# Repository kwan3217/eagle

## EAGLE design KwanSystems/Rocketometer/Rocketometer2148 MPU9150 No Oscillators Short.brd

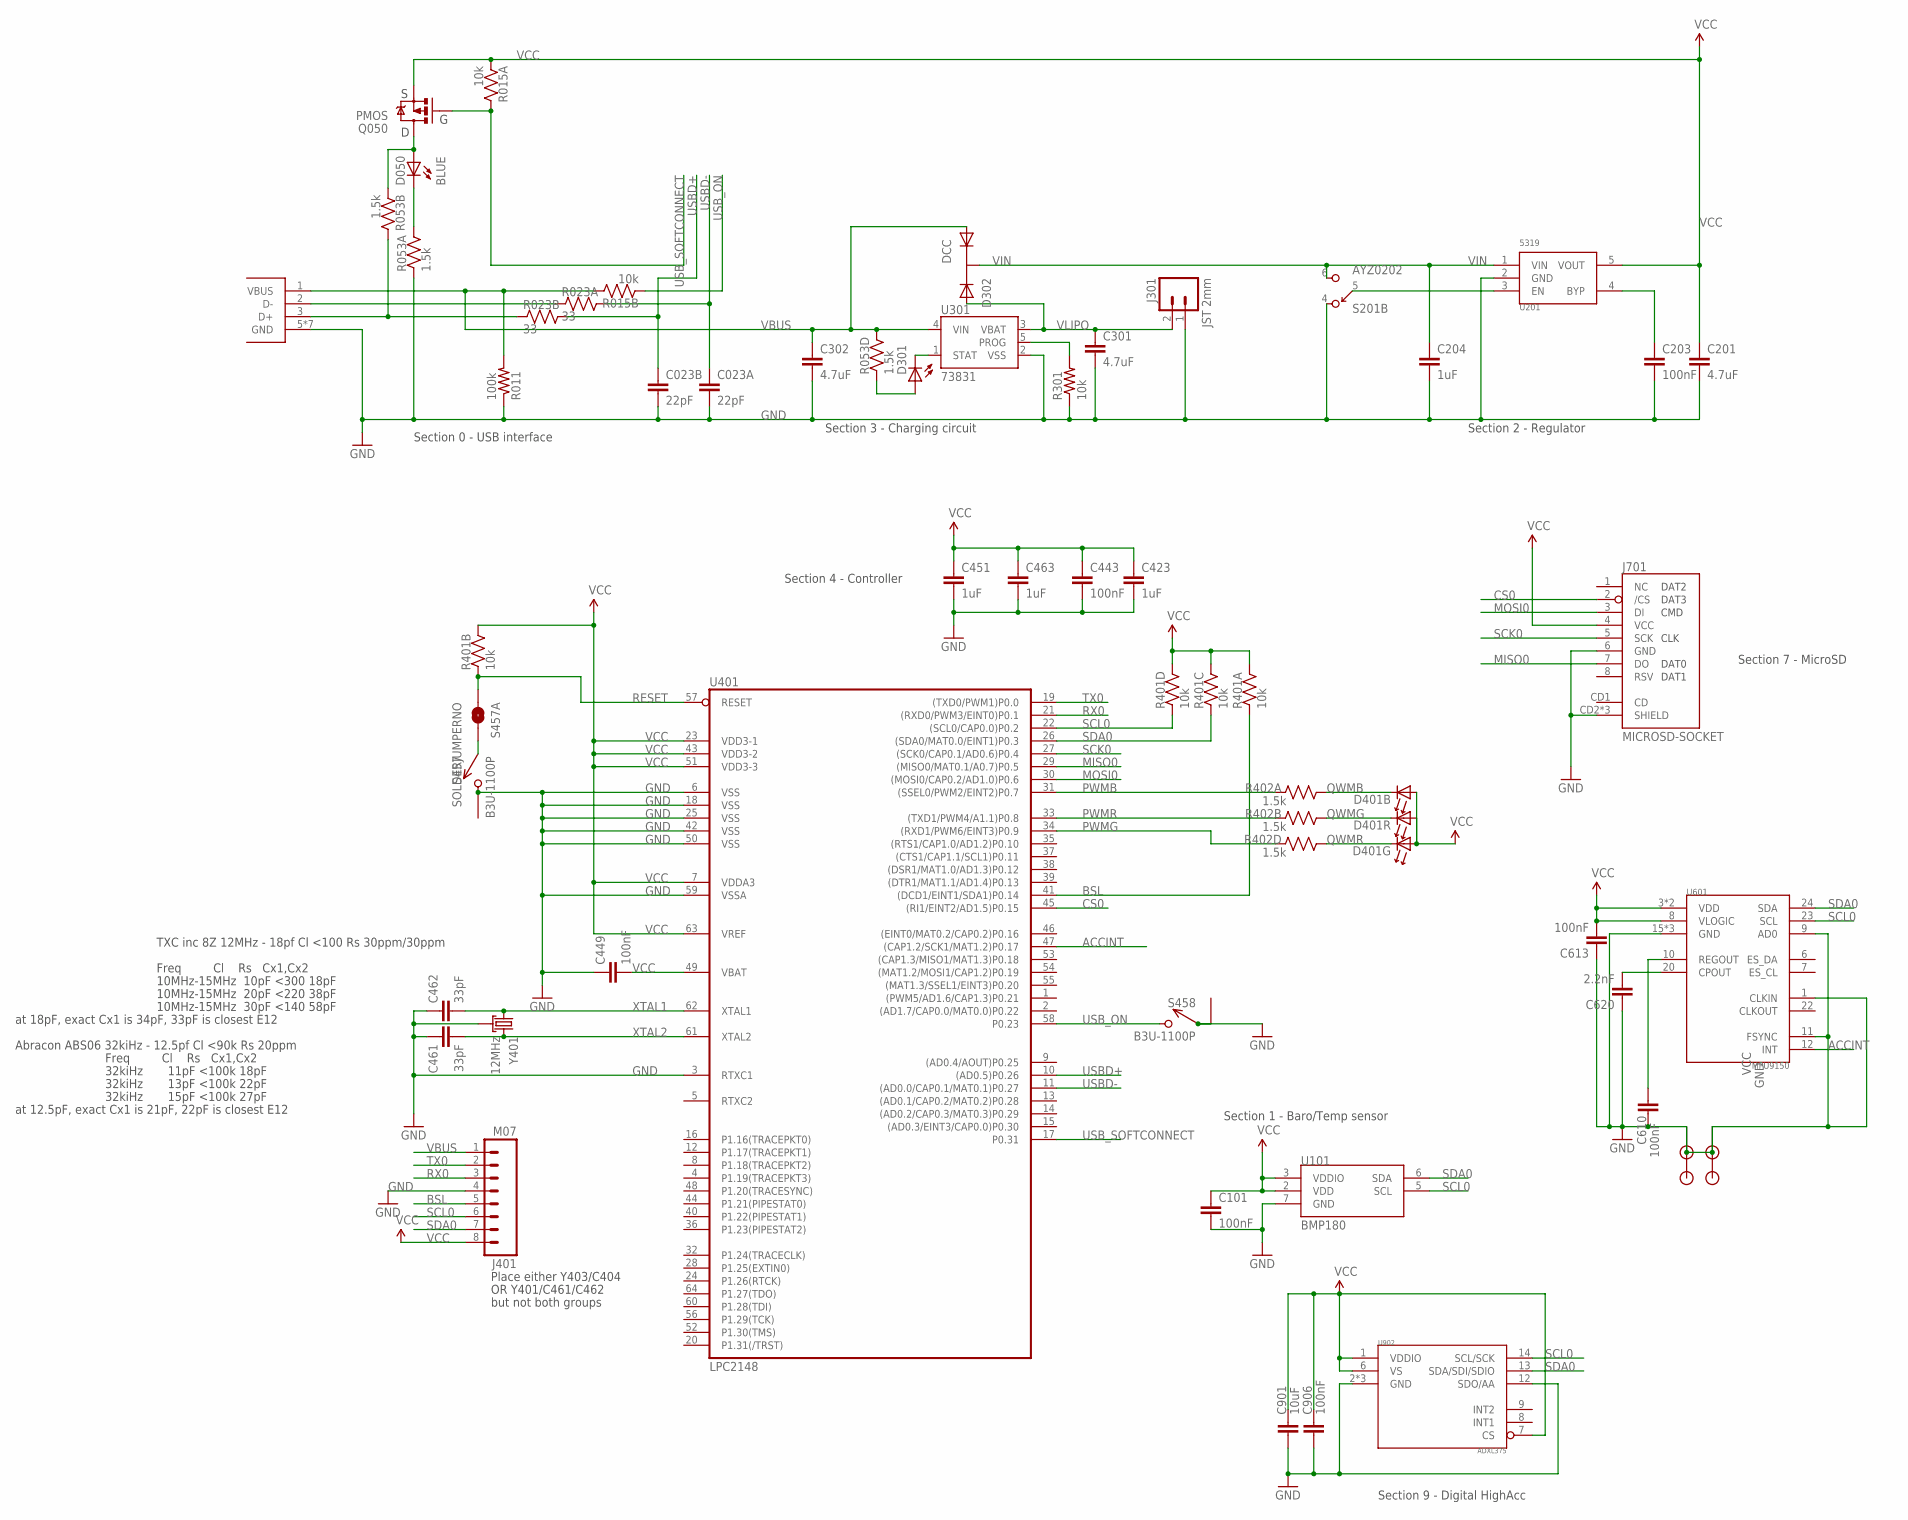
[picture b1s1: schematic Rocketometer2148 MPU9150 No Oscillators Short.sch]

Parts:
C023: 22pF; CKCM25; DIGIKEY 445-1860-1-ND
C101, C203, C443, C449, C610, C613, C906: 100nF; 0402-CAP; DIGIKEY 445-1265-1-ND
C201, C301, C302: 4.7uF; 0402-CAP; DIGIKEY 445-7395-1-ND
C204, C423, C451, C463: 1uF; 0402-CAP; DIGIKEY 445-4114-1-ND
C461, C462: 33pF; 0402-CAP; DIGIKEY 445-1241-1-ND
C620: 2.2nF; 0402-CAP; DIGIKEY 445-1257-1-ND
C901: 10uF; 0603-CAP; DIGIKEY 445-7486-1-ND
D050: BLUE; LED-0603; DIGIKEY 350-2037-1-ND
D301: YELLOW; LED-0603; DIGIKEY 350-2032-1-ND
D302: DCC; SOT-23-3; DIGIKEY 568-6500-1-ND
D401: SMLP36RGB2W(R); SMLP36; DIGIKEY 846-1097-1-ND
J001: USB_MICROB_JSTGCT; USB_MICROB_3075; DIGIKEY 609-4616-2-ND
J301: JST 2mm; JST-2-SMD; DIGIKEY 455-1749-1-ND
J401: M07; 1X08; DIGIKEY $NOPART
J701: MICROSD-SOCKET; MICROSD-SOCKET-PP; DIGIKEY 101-00581-59-1-ND
JP1, JP2, JP4, JP5: STANDOFF; DIGIKEY $NOPART
Q050: PMOS; SOT23-3; DIGIKEY NTR1P02T1GOSCT-ND
R011: 100k; 0402-RES; DIGIKEY P100KLCT-ND
R015: 10k; CRA02; DIGIKEY Y5103CT-ND
R023: 33; CRA02
R053, R402: 1.5k; CRA04; DIGIKEY CRA4S81.5KCT-ND
R301: 10k; 0402-RES; DIGIKEY P10.0KLCT-ND
R401: 10k; CRA04; DIGIKEY CRA4S810KCT-ND
S201: AYZ0202; DIGIKEY 401-2013-1-ND
S457, S458: B3U-1100P; DIGIKEY SW1021CT-ND
S457A: SOLDERJUMPERNO; SJ_2S-NO; DIGIKEY $NOPART
U101: BMP180; DIGIKEY 828-1027-1-ND
U201: 5319; SOT-23-5; DIGIKEY 576-1910-1-ND
U301: 73831; SOT23-5; DIGIKEY MCP73831T-2ACI/OTCT-ND
U401: LPC2148; SQFP-S-10X10-64; DIGIKEY 568-1765-ND
U601: MPU9150; LLGA24; DIGIKEY $NOPART
U902: ADXL375; DIGIKEY ADXL375BCCZ-ND
Y401: 12MHz; CRYSTAL_SMD_2MM_2_5MM; DIGIKEY 887-1487-1-ND

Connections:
ACCINT: U401.47 ((CAP1.2/SCK1/MAT1.2)P0.17), U601.12 (INT)
BSL: J401.5, R401.1, U401.41 ((DCD1/EINT1/SDA1)P0.14)
CONN_D+: J001.3 (D+), R023.2 (1), R053.7 (2)
CONN_D-: J001.2 (D-), R023.1
CS0: J701.2 (/CS), U401.45 ((RI1/EINT2/AD1.5)P0.15)
EN: S201.5, U201.3 (EN)
GND: C023.3 (2), C023.4 (2), C101.2, C201.2, C203.2, C204.2, C301.2, C302.2, C423.2, C443.2, C449.1, C451.2, C461.1, C462.1, C463.2, C610.2, C613.1, C620.1, C901.2, C906.2, J001.5 (GND), J001.P$1 (GND), J001.P$2 (GND), J001.P$3 (GND), J001.P$4 (GND), J001.P$8 (GND), J001.P$10 (GND), J301.1, J401.4, J701.6 (GND), J701.CD2 (SHIELD), J701.GND1 (SHIELD), J701.GND3 (SHIELD), JP1.P$1, JP2.P$1, JP4.P$1, JP5.P$1, R011.1, R053.1, R301.1, S201.4, S457.P$2 (2), S457.P$3 (1), S458.P$1 (1), S458.P$3 (1), U101.7 (GND), U201.2 (GND), U301.2 (VSS), U401.3 (RTXC1), U401.6 (VSS), U401.18 (VSS), U401.25 (VSS), U401.42 (VSS), U401.50 (VSS), U401.59 (VSSA), U601.1 (CLKIN), U601.9 (AD0), U601.11 (FSYNC), U601.15 (GND), U601.17 (GND), U601.18 (GND), U902.2 (GND), U902.4 (GND), U902.5 (GND), U902.12 (SDO/AA), Y401.2 (GND), Y401.4 (GND)
MISO0: J701.7 (DO), U401.29 ((MISO0/MAT0.1/A0.7)P0.5)
MOSI0: J701.3 (DI), U401.30 ((MOSI0/CAP0.2/AD1.0)P0.6)
unnamed: C620.2, U601.20 (CPOUT)
unnamed: R301.2, U301.5 (PROG)
unnamed: D301.A, R053.4 (1)
unnamed: D301.C, U301.1 (STAT)
unnamed: D050.A, Q050.3 (D), R053.2 (1)
unnamed: D050.C, R053.8 (2)
unnamed: S457.P$1 (1), S457A.2
unnamed: C610.1, U601.10 (REGOUT)
unnamed: C203.1, U201.4 (BYP)
PWMB: R402.8 (2), U401.31 ((SSEL0/PWM2/EINT2)P0.7)
PWMG: R402.5 (2), U401.34 ((RXD1/PWM6/EINT3)P0.9)
PWMR: R402.7 (2), U401.33 ((TXD1/PWM4/A1.1)P0.8)
QWMB: D401.1 (C), R402.1
QWMG: D401.5 (C), R402.4 (1)
QWMR: D401.3 (C), R402.2 (1)
RESET: R401.2 (1), S457A.1, U401.57 (RESET)
RX0: J401.3, U401.21 ((RXD0/PWM3/EINT0)P0.1)
SCK0: J701.5 (SCK), U401.27 ((SCK0/CAP0.1/AD0.6)P0.4)
SCL0: J401.6, R401.4 (1), U101.5 (SCL), U401.22 ((SCL0/CAP0.0)P0.2), U601.23 (SCL), U902.14 (SCL/SCK)
SDA0: J401.7, R401.3 (1), U101.6 (SDA), U401.26 ((SDA0/MAT0.0/EINT1)P0.3), U601.24 (SDA), U902.13 (SDA/SDI/SDIO)
TX0: J401.2, U401.19 ((TXD0/PWM1)P0.0)
USBD+: C023.2 (1), R023.3 (2), U401.10 ((AD0.5)P0.26)
USBD-: C023.1, R023.4 (2), U401.11 ((AD0.0/CAP0.1/MAT0.1)P0.27)
USB_ON: R015.2 (1), S458.P$2 (2), U401.58 (P0.23)
USB_SOFTCONNECT: Q050.1 (G), R015.4 (2), U401.17 (P0.31)
VBUS: C302.1, D302.1 (A1), J001.1 (VBUS), J401.1, R011.2, R015.3 (2), R053.5 (2), U301.4 (VIN)
VCC: C101.1, C201.1, C423.1, C443.1, C449.2, C451.1, C463.1, C613.2, C901.1, C906.1, D401.2 (A), D401.4 (A), D401.6 (A), J401.8, J701.4 (VCC), Q050.2 (S), R015.1, R401.5 (2), R401.6 (2), R401.7 (2), R401.8 (2), U101.2 (VDD), U101.3 (VDDIO), U201.5 (VOUT), U401.7 (VDDA3), U401.23 (VDD3-1), U401.43 (VDD3-2), U401.49 (VBAT), U401.51 (VDD3-3), U401.63 (VREF), U601.3 (VDD), U601.8 (VLOGIC), U601.13 (VDD), U902.1 (VDDIO), U902.6 (VS), U902.7 (CS)
VIN: C204.1, D302.3 (K), S201.6, U201.1 (VIN)
VLIPO: C301.1, D302.2 (A2), J301.2, U301.3 (VBAT)
XTAL1: C462.2, U401.62 (XTAL1), Y401.1
XTAL2: C461.2, U401.61 (XTAL2), Y401.3 (2)

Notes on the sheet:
Section 4 - Controller
Section 7 - MicroSD
Section 1 - Baro/Temp sensor
Freq Cl Rs Cx1,Cx2
10MHz-15MHz 10pF <300 18pF
10MHz-15MHz 20pF <220 38pF
10MHz-15MHz 30pF <140 58pF
TXC inc 8Z 12MHz - 18pf Cl <100 Rs 30ppm/30ppm
at 18pF, exact Cx1 is 34pF, 33pF is closest E12
32kiHz 11pF <100k 18pF
32kiHz 13pF <100k 22pF
32kiHz 15pF <100k 27pF
Abracon ABS06 32kiHz - 12.5pf Cl <90k Rs 20ppm
at 12.5pF, exact Cx1 is 21pF, 22pF is closest E12
Section 2 - Regulator
Section 3 - Charging circuit
Section 0 - USB interface
Place either Y403/C404
OR Y401/C461/C462
but not both groups
Section 9 - Digital HighAcc

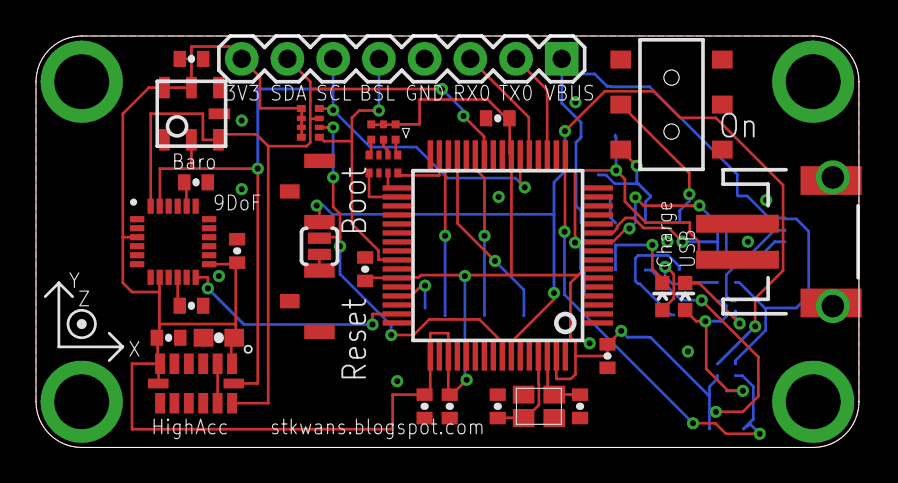
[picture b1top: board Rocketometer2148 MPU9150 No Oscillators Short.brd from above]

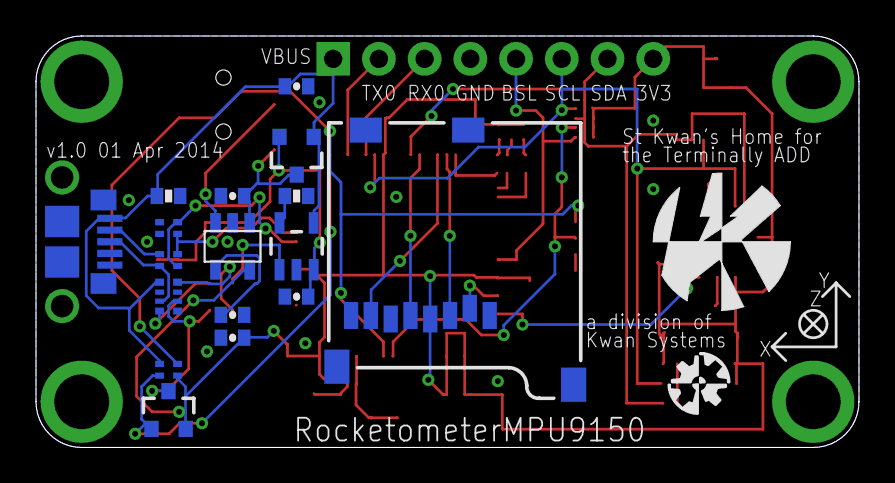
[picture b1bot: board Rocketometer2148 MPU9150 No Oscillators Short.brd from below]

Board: 2 copper layers, 45.7 x 22.9 mm, 53 parts (19 on the bottom side), 40 nets.

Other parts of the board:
U$4: AXES
U$5: KWAN_ACC
U$6: OSHW_ACC

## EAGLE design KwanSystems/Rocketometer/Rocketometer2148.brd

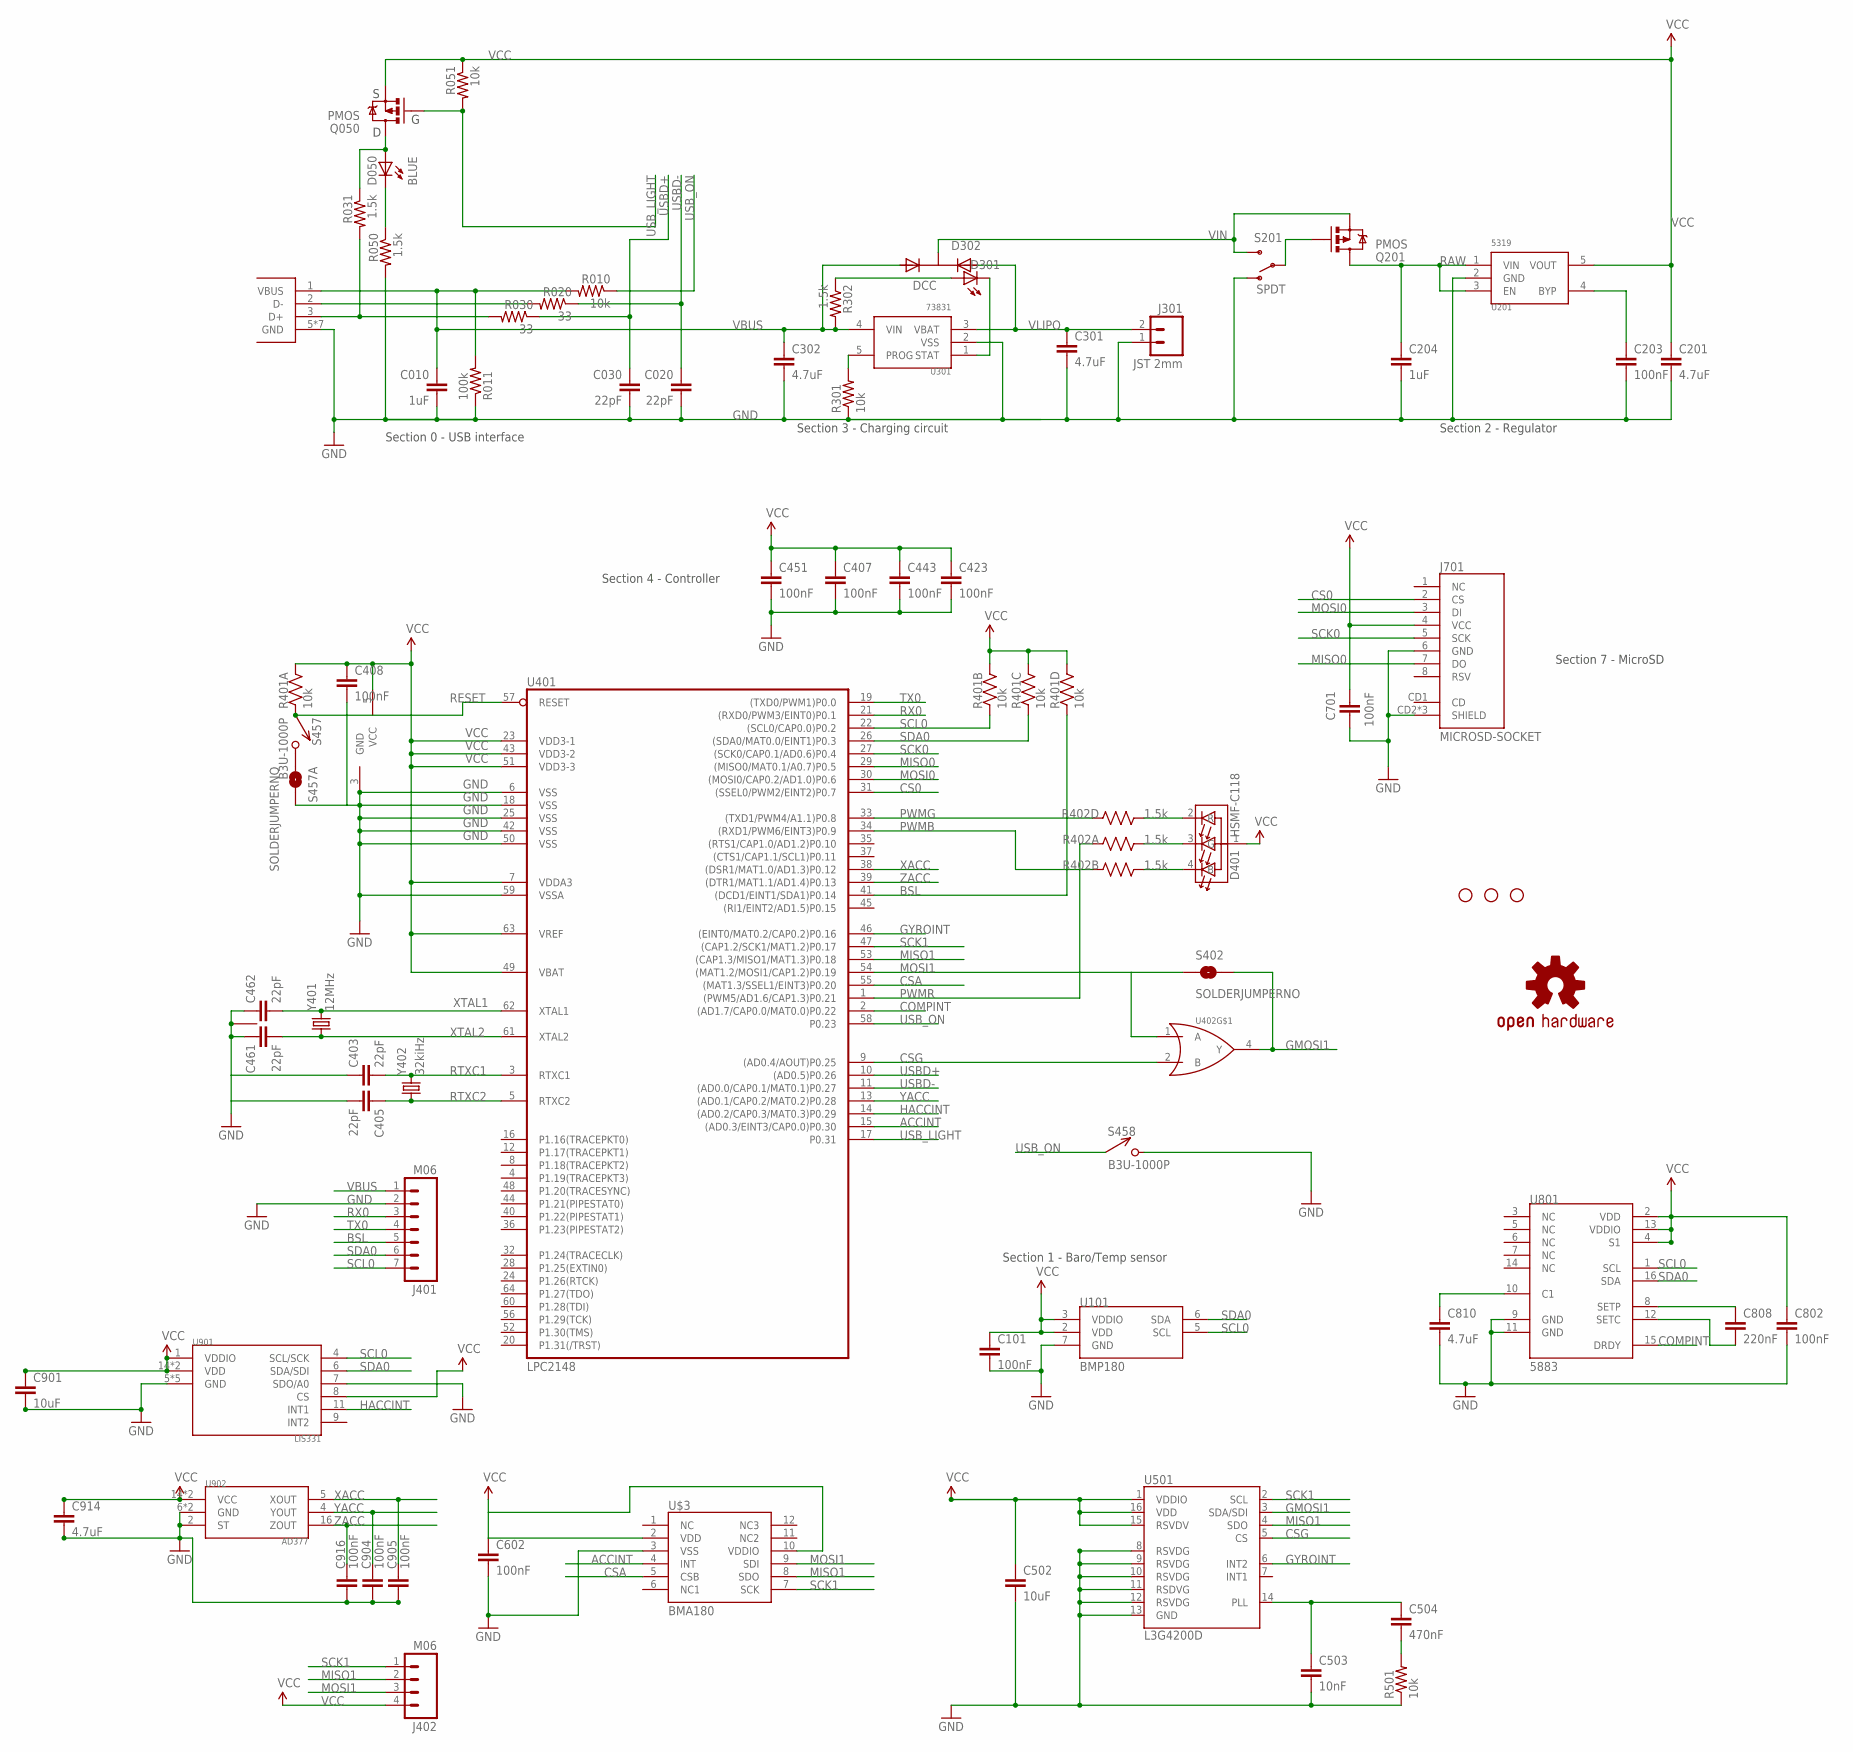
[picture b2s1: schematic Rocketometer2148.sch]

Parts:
C010, C204: 1uF; 0402-CAP; DIGIKEY 445-1415-1-ND
C020, C030, C403, C405, C461, C462: 22pF; 0402-CAP; DIGIKEY 445-1239-1-ND
C101, C203, C407, C408, C423, C443, C451, C701, C802, C904, C905, C916: 100nF; 0402-CAP; DIGIKEY 445-1268-1-ND
C201, C301, C302, C810, C914: 4.7uF; 0402-CAP; DIGIKEY 445-7395-1-ND
C502, C901: 10uF; 0603-CAP; DIGIKEY 445-7486-1-ND
C503: 10nF; 0402-CAP; DIGIKEY 445-4943-1-ND
C504: 470nF; 0402-CAP; DIGIKEY 445-4976-1-ND
C602: 100nF; 0402-CAP; DIGIKEY 445-7395-1-ND
C808: 220nF; 0402-CAP; DIGIKEY 445-4972-1-ND
D050: BLUE; LED-0603; DIGIKEY 754-1434-1-ND
D301: YELLOW; LED-0603; DIGIKEY 754-1354-1-ND
D302: DCC; SOT-23-3; DIGIKEY 568-6500-1-ND
D401: HSMF-C118; DIGIKEY 516-1778-1-ND
J001: USB_MICROB_JST; UB-MC5BR3-SD204-4S; DIGIKEY 455-2562-1-ND
J301: JST 2mm; JST-2-SMD; DIGIKEY 455-1749-1-ND
J401: M06; 1X07; DIGIKEY $NOPART
J402: M06; 1X04; DIGIKEY $NOPART
J701: MICROSD-SOCKET; MICROSD-SOCKET-PP; DIGIKEY 101-00581-59-1-ND
JP1, JP2, JP3: STAND-OFFTIGHT; STAND-OFF-TIGHT; DIGIKEY $NOPART
Q050, Q201: PMOS; SOT23-3; DIGIKEY NTR1P02T1GOSCT-ND
R010, R051, R301, R501: 10k; 0402-RES; DIGIKEY P10.0KLCT-ND
R011: 100k; 0402-RES; DIGIKEY P100KLCT-ND
R020, R030: 33; 0402-RES; DIGIKEY P33.0LCT-ND
R031, R050, R302: 1.5k; 0402-RES; DIGIKEY P1.50KLCT-ND
R401: 10k; CRA04; DIGIKEY CRA4S810KCT-ND
R402: 1.5k; CRA04; DIGIKEY CRA4S81.5KCT-ND
S201: SPDT; AYZ0202; DIGIKEY 401-2013-1-ND
S402, S457A: SOLDERJUMPERNO; SJ_2S-NO; DIGIKEY $NOPART
S457, S458: B3U-1000P; DIGIKEY SW1020CT-ND
U101: BMP180; DIGIKEY 828-1027-1-ND
U201: 5319; SOT-23-5; DIGIKEY 576-1910-1-ND
U301: 73831; SOT-23-5; DIGIKEY MCP73831T-2ACI/OTCT-ND
U401: LPC2148; SQFP-S-10X10-64; DIGIKEY 568-1765-ND
U402: SN74LVC1G32; SOT-23-5
U501: L3G4200D; LGA16-4X4; DIGIKEY 497-11071-1-ND
U801: 5883; 16LPCC; DIGIKEY 342-1082-1-ND
U901: LIS331; LLGA16
U902: AD377; ADXL377
U$2: OSHW-LOGOS; OSHW-LOGO-S; DIGIKEY $NOPART
U$3: BMA180; LGA12
Y401: 12MHz; CRYSTAL_SMD_2MM_2_5MM
Y402: 32kiHz; ABS06; DIGIKEY 535-10248-1-ND

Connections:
ACCINT: U401.15 ((AD0.3/EINT3/CAP0.0)P0.30), U$3.4 (INT)
BSL: J401.5, R401.4 (1), U401.41 ((DCD1/EINT1/SDA1)P0.14)
COMPINT: U401.2 ((AD1.7/CAP0.0/MAT0.0)P0.22), U801.15 (DRDY)
CONN_D+: J001.3 (D+), R030.2, R031.2
CONN_D-: J001.2 (D-), R020.2
CS0: J701.2 (CS), U401.31 ((SSEL0/PWM2/EINT2)P0.7)
CSA: U401.55 ((MAT1.3/SSEL1/EINT3)P0.20), U$3.5 (CSB)
CSG: U401.9 ((AD0.4/AOUT)P0.25), U402.2 (B), U501.5 (CS)
GMOSI1: S402.2, U402.4 (Y), U501.3 (SDA/SDI)
GND: C010.2, C020.2, C030.2, C101.2, C201.2, C203.2, C204.2, C301.2, C302.2, C403.1, C405.2, C407.2, C408.2, C423.2, C443.2, C451.2, C461.1, C462.1, C502.2, C503.2, C602.2, C701.2, C802.2, C810.2, C901.2, C904.2, C905.2, C914.2, C916.2, J001.5 (GND), J001.P$6 (GND), J001.P$7 (GND), J001.P$8 (GND), J001.P$9 (GND), J001.P$10 (GND), J001.P$11 (GND), J301.1, J401.2, J701.6 (GND), J701.CD2 (SHIELD), J701.GND1 (SHIELD), J701.GND3 (SHIELD), R011.1, R050.2, R301.1, R501.1, S201.1 (O), S457A.2, S458.P$2 (2), U101.7 (GND), U201.2 (GND), U301.2 (VSS), U401.6 (VSS), U401.18 (VSS), U401.25 (VSS), U401.42 (VSS), U401.50 (VSS), U401.59 (VSSA), U402.3 (GND), U501.8 (RSVDG), U501.9 (RSVDG), U501.10 (RSVDG), U501.11 (RSDVG), U501.12 (RSVDG), U501.13 (GND), U801.9 (GND), U801.11 (GND), U901.5 (GND), U901.7 (SDO/A0), U901.10 (GND), U901.12 (GND), U901.13 (GND), U901.16 (GND), U902.2 (ST), U902.6 (GND), U902.7 (GND), U$3.3 (VSS), Y401.2 (1), Y401.4 (1)
GYROINT: U401.46 ((EINT0/MAT0.2/CAP0.2)P0.16), U501.6 (INT2)
HACCINT: U401.14 ((AD0.2/CAP0.3/MAT0.3)P0.29), U901.11 (INT1)
MISO0: J701.7 (DO), U401.29 ((MISO0/MAT0.1/A0.7)P0.5)
MISO1: J402.2, U401.53 ((CAP1.3/MISO1/MAT1.3)P0.18), U501.4 (SDO), U$3.8 (SDO)
MOSI0: J701.3 (DI), U401.30 ((MOSI0/CAP0.2/AD1.0)P0.6)
MOSI1: J402.3, S402.1, U401.54 ((MAT1.2/MOSI1/CAP1.2)P0.19), U402.1 (A), U$3.9 (SDI)
unnamed: C504.2, R501.2
unnamed: R301.2, U301.5 (PROG)
unnamed: D401.4 (B), R402.2 (1)
unnamed: D301.C, U301.1 (STAT)
unnamed: D301.A, R302.1
unnamed: D050.A, Q050.3 (D), R031.1
unnamed: D050.C, R050.1
unnamed: S457.P$2 (2), S457A.1
unnamed: D401.2 (R), R402.4 (1)
unnamed: Q201.1 (G), S201.2
unnamed: D401.3 (G), R402.1
unnamed: C808.1, U801.8 (SETP)
unnamed: C808.2, U801.12 (SETC)
unnamed: C810.1, U801.10 (C1)
unnamed: C203.1, U201.4 (BYP)
unnamed: C503.1, C504.1, U501.14 (PLL)
PWMB: R402.7 (2), U401.34 ((RXD1/PWM6/EINT3)P0.9)
PWMG: R402.5 (2), U401.33 ((TXD1/PWM4/A1.1)P0.8)
PWMR: R402.8 (2), U401.1 ((PWM5/AD1.6/CAP1.3)P0.21)
RAW: C204.1, Q201.3 (D), U201.1 (VIN), U201.3 (EN)
RESET: R401.1, S457.P$1 (1), U401.57 (RESET)
RTXC1: C403.2, U401.3 (RTXC1), Y402.2
RTXC2: C405.1, U401.5 (RTXC2), Y402.1
RX0: J401.3, U401.21 ((RXD0/PWM3/EINT0)P0.1)
SCK0: J701.5 (SCK), U401.27 ((SCK0/CAP0.1/AD0.6)P0.4)
SCK1: J402.1, U401.47 ((CAP1.2/SCK1/MAT1.2)P0.17), U501.2 (SCL), U$3.7 (SCK)
SCL0: J401.7, R401.2 (1), U101.5 (SCL), U401.22 ((SCL0/CAP0.0)P0.2), U801.1 (SCL), U901.4 (SCL/SCK)
SDA0: J401.6, R401.3 (1), U101.6 (SDA), U401.26 ((SDA0/MAT0.0/EINT1)P0.3), U801.16 (SDA), U901.6 (SDA/SDI)
TX0: J401.4, U401.19 ((TXD0/PWM1)P0.0)
USBD+: C030.1, R030.1, U401.10 ((AD0.5)P0.26)
USBD-: C020.1, R020.1, U401.11 ((AD0.0/CAP0.1/MAT0.1)P0.27)
USB_LIGHT: Q050.1 (G), R051.2, U401.17 (P0.31)
USB_ON: R010.1, S458.P$1 (1), U401.58 (P0.23)
VBUS: C010.1, C302.1, D302.1 (A1), J001.1 (VBUS), J401.1, R010.2, R011.2, R302.2, U301.4 (VIN)
VCC: C101.1, C201.1, C407.1, C408.1, C423.1, C443.1, C451.1, C502.1, C602.1, C701.1, C802.1, C901.1, C914.1, D401.1 (A), J402.4, J701.4 (VCC), Q050.2 (S), R051.1, R401.5 (2), R401.6 (2), R401.7 (2), R401.8 (2), U101.2 (VDD), U101.3 (VDDIO), U201.5 (VOUT), U401.7 (VDDA3), U401.23 (VDD3-1), U401.43 (VDD3-2), U401.49 (VBAT), U401.51 (VDD3-3), U401.63 (VREF), U402.5 (VCC), U501.1 (VDDIO), U501.15 (RSVDV), U501.16 (VDD), U801.2 (VDD), U801.4 (S1), U801.13 (VDDIO), U901.1 (VDDIO), U901.8 (CS), U901.14 (VDD), U901.15 (VDD), U902.14 (VCC), U902.15 (VCC), U$3.2 (VDD), U$3.10 (VDDIO)
VIN: D302.3 (K), Q201.2 (S), S201.3 (S)
VLIPO: C301.1, D302.2 (A2), J301.2, U301.3 (VBAT)
XACC: C905.1, U401.38 ((DSR1/MAT1.0/AD1.3)P0.12), U902.5 (XOUT)
XTAL1: C462.2, U401.62 (XTAL1), Y401.3 (2)
XTAL2: C461.2, U401.61 (XTAL2), Y401.1
YACC: C904.1, U401.13 ((AD0.1/CAP0.2/MAT0.2)P0.28), U902.4 (YOUT)
ZACC: C916.1, U401.39 ((DTR1/MAT1.1/AD1.4)P0.13), U902.16 (ZOUT)

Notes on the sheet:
Section 2 - Regulator
Section 3 - Charging circuit
Section 0 - USB interface
Section 4 - Controller
Section 7 - MicroSD
Section 1 - Baro/Temp sensor

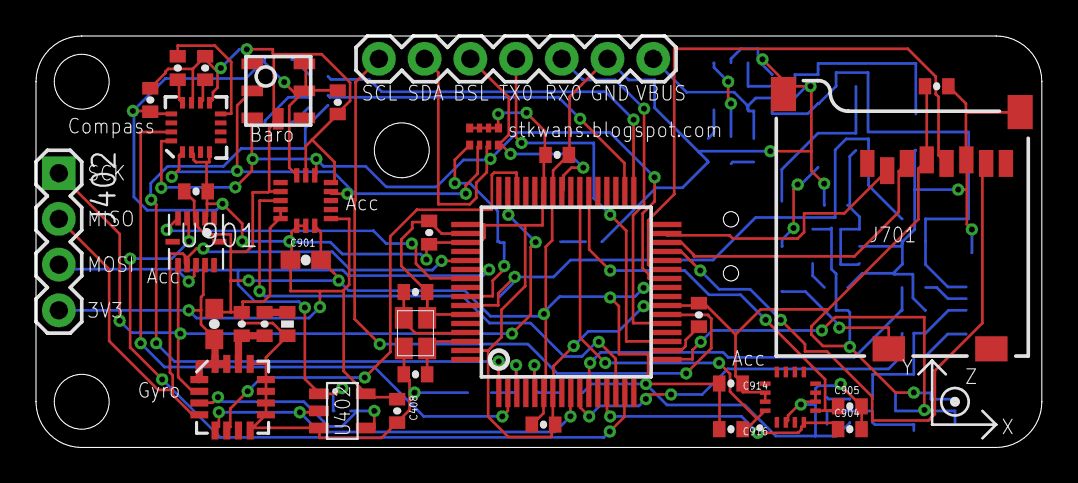
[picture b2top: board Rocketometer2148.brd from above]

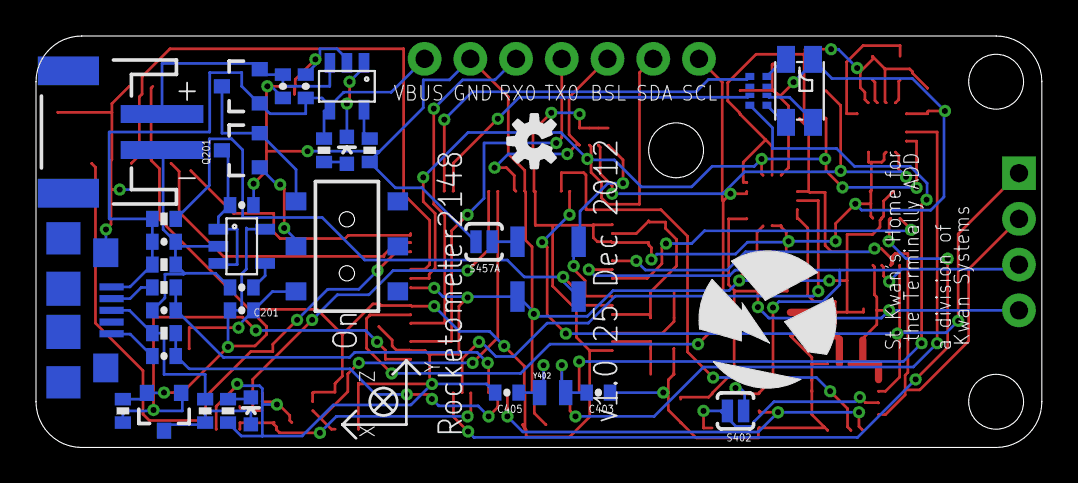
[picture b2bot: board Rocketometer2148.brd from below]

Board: 2 copper layers, 55.9 x 22.9 mm, 76 parts (38 on the bottom side), 58 nets.

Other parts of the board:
U$1: KWAN_CIRCLE

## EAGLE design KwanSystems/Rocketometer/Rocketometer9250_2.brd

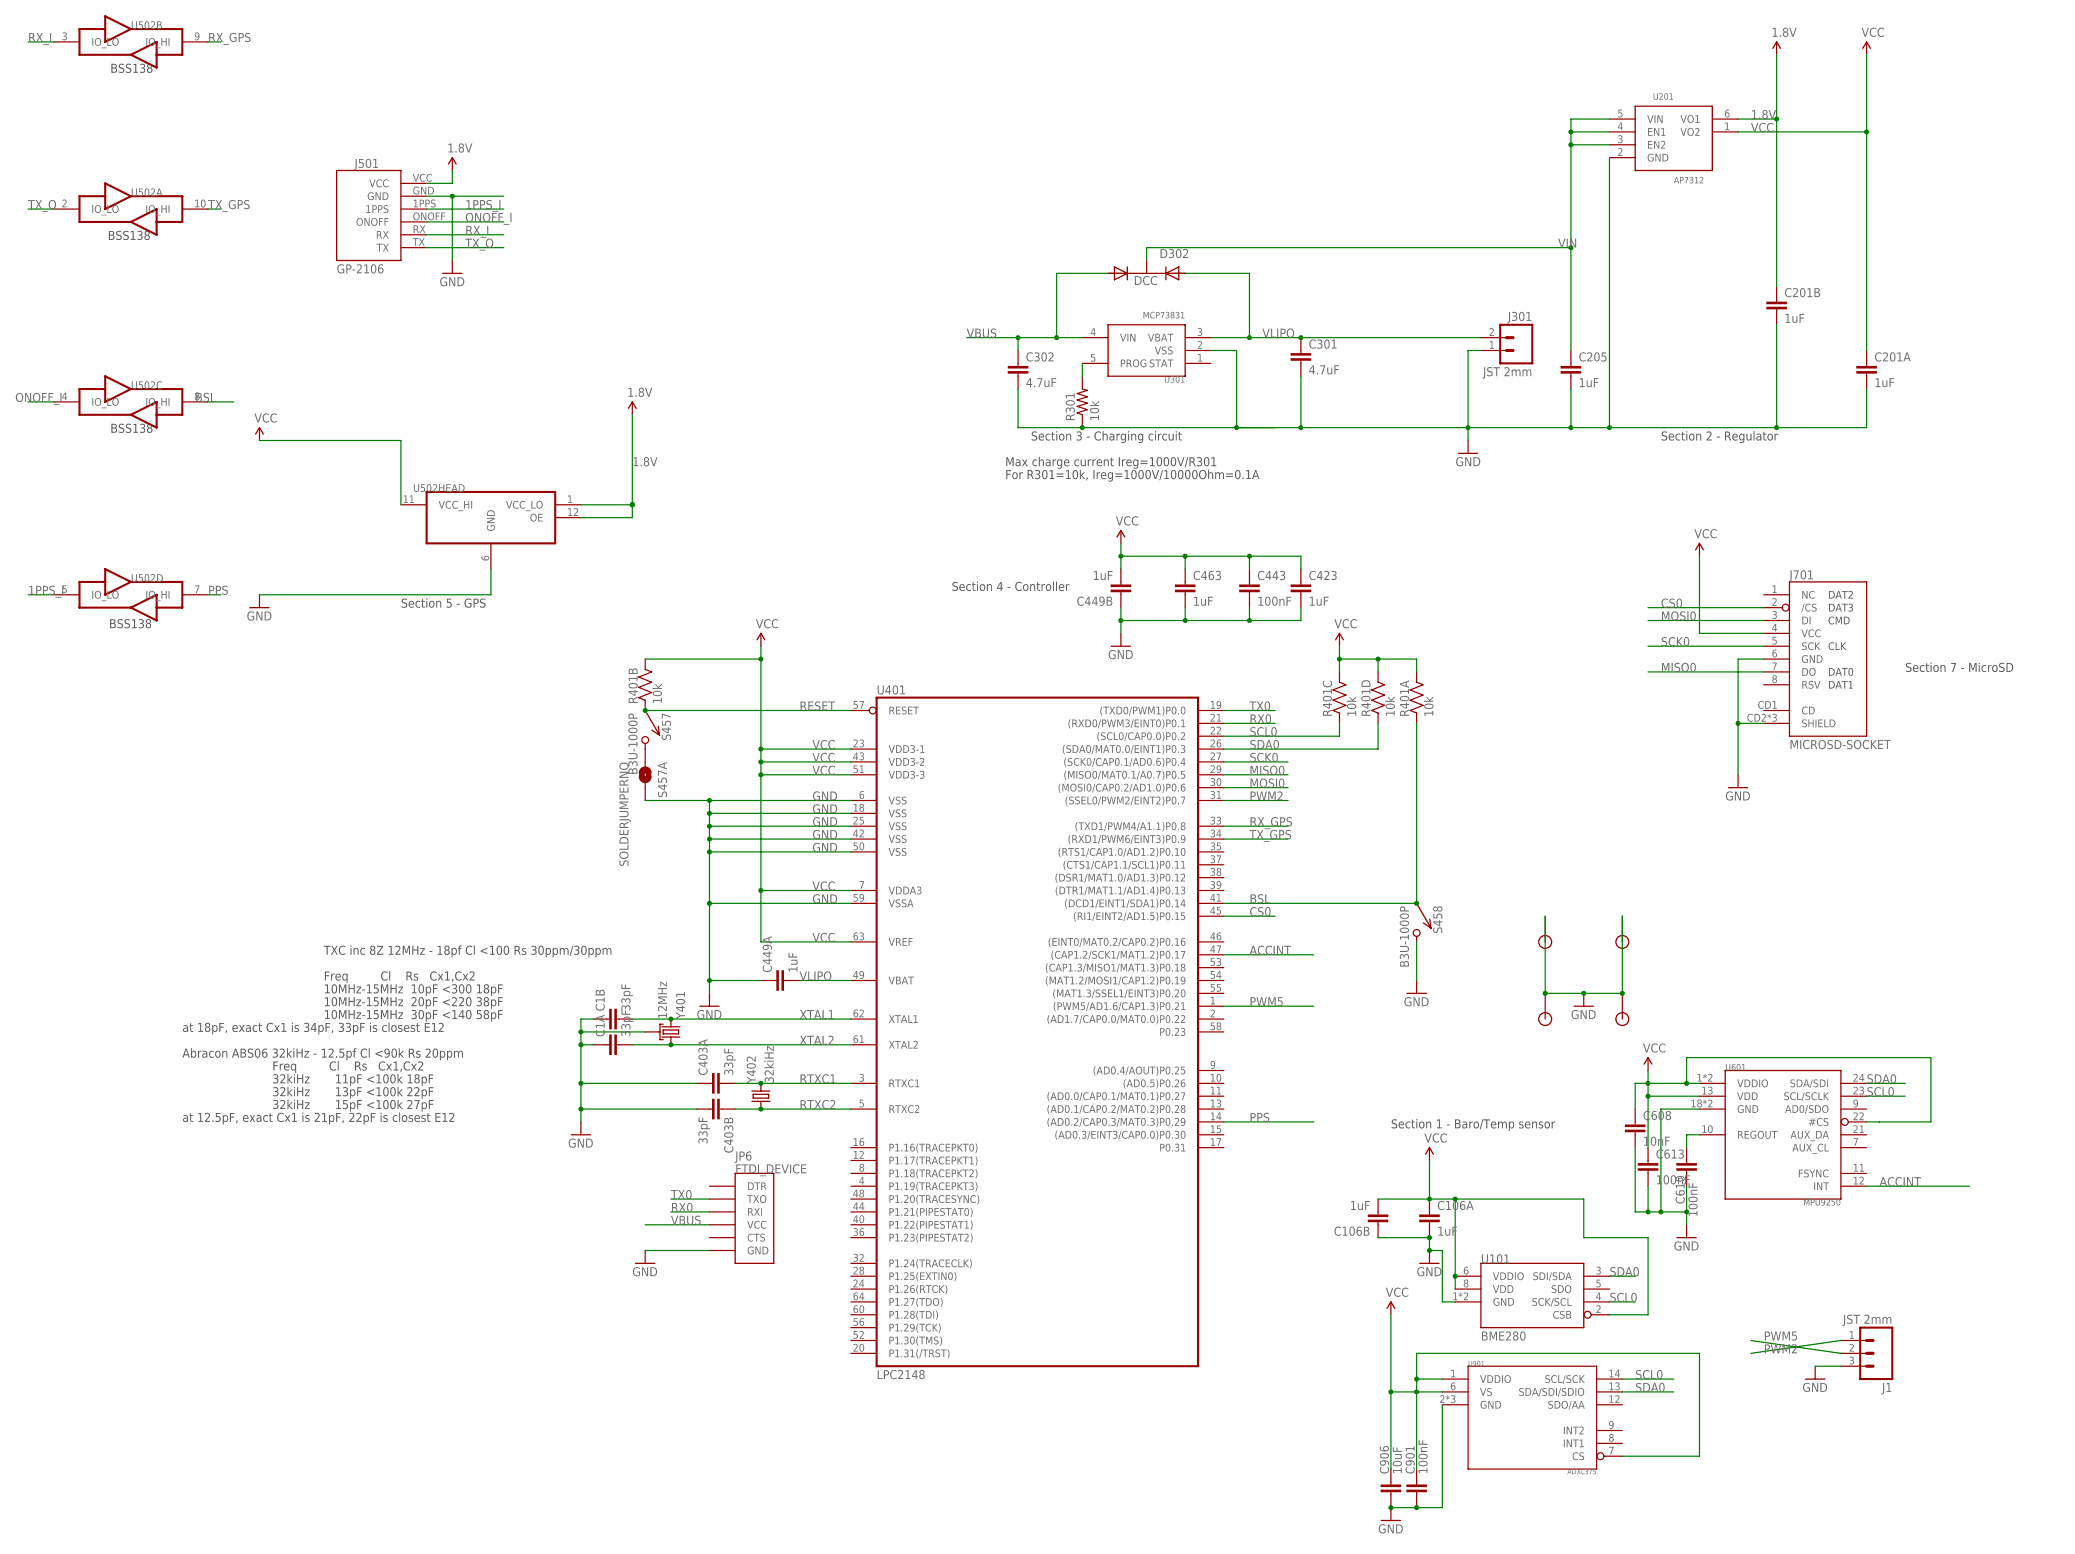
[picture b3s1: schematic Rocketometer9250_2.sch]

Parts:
C1, C403: 33pF; CKCM25
C106, C201, C449: 1uF; CKCM25
C205, C423, C463: 1uF; 0402-CAP; DIGIKEY 445-4114-1-ND
C301, C302: 4.7uF; 0402-CAP; DIGIKEY 445-7395-1-ND
C443, C610, C613, C901: 100nF; 0402-CAP; DIGIKEY 445-1265-1-ND
C608: 10nF; 0402-CAP; DIGIKEY 445-1257-1-ND
C906: 10uF; 0603-CAP; DIGIKEY 445-7486-1-ND
D302: DCC; SOT-23-3; DIGIKEY 568-6500-1-ND
J1: JST 2mm; 1X03_NO_SILK; DIGIKEY 455-1749-1-ND
J301: JST 2mm; 1X02_NO_SILK; DIGIKEY 455-1749-1-ND
J501: GP-2106
J701: MICROSD-SOCKET; MICROSD-SOCKET-PP; DIGIKEY 101-00581-59-1-ND
JP1, JP2, JP4, JP5: STANDOFF; DIGIKEY $NOPART
JP6: FTDI_DEVICE; FTDI_DEVICE_SIDE
R301: 10k; 0402-RES; DIGIKEY P10.0KLCT-ND
R401: 10k; CRA04; DIGIKEY CRA4S810KCT-ND
S457, S458: B3U-1000P; DIGIKEY SW1020CT-ND
S457A: SOLDERJUMPERNO; SJ_2S-NO; DIGIKEY $NOPART
U101: BME280
U201: AP7312; SOT-23-6
U301: MCP73831; SOT-23-5; DIGIKEY 576-1910-1-ND
U401: LPC2148; SQFP-S-10X10-64; DIGIKEY 568-1765-ND
U502: TXB0104RUT; R-PUQFN-N12
U601: MPU9250; LQFN_3MM_3MM
U901: ADXL375
Y401: 12MHz; CRYSTAL_SMD_2MM_2_5MM; DIGIKEY 887-1487-1-ND
Y402: 32kiHz; ABS06; DIGIKEY 535-10104-1-ND

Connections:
1.8V: C201.2 (1), J501.VCC, U201.6 (VO1), U502.1 (VCC_LO), U502.12 (OE)
1PPS_I: J501.1PPS, U502.5 (IO_LO)
ACCINT: U401.47 ((CAP1.2/SCK1/MAT1.2)P0.17), U601.12 (INT)
BSL: R401.1, S458.P$1 (1), U401.41 ((DCD1/EINT1/SDA1)P0.14), U502.8 (IO_HI)
CS0: J701.2 (/CS), U401.45 ((RI1/EINT2/AD1.5)P0.15)
GND: C1.1, C1.2 (1), C106.2 (1), C106.4 (2), C201.3 (2), C201.4 (2), C205.2, C301.2, C302.2, C403.1, C403.3 (2), C423.2, C443.2, C449.1, C449.2 (1), C463.2, C608.2, C610.2, C613.2, C901.2, C906.2, J1.3, J301.1, J501.GND, J701.6 (GND), J701.CD2 (SHIELD), J701.GND1 (SHIELD), J701.GND3 (SHIELD), JP1.P$1, JP2.P$1, JP4.P$1, JP5.P$1, JP6.P$6 (GND), R301.1, S457A.2, S458.P$2 (2), U101.1 (GND), U101.7 (GND), U201.2 (GND), U301.2 (VSS), U401.6 (VSS), U401.18 (VSS), U401.25 (VSS), U401.42 (VSS), U401.50 (VSS), U401.59 (VSSA), U502.6 (GND), U601.18 (GND), U601.20 (GND), U901.2 (GND), U901.4 (GND), U901.5 (GND), Y401.2 (GND), Y401.4 (GND)
MISO0: J701.7 (DO), U401.29 ((MISO0/MAT0.1/A0.7)P0.5)
MOSI0: J701.3 (DI), U401.30 ((MOSI0/CAP0.2/AD1.0)P0.6)
unnamed: R301.2, U301.5 (PROG)
unnamed: S457.P$2 (2), S457A.1
unnamed: C610.1, U601.10 (REGOUT)
ONOFF_I: J501.ONOFF, U502.4 (IO_LO)
PPS: U401.14 ((AD0.2/CAP0.3/MAT0.3)P0.29), U502.7 (IO_HI)
PWM2: J1.1, U401.31 ((SSEL0/PWM2/EINT2)P0.7)
PWM5: J1.2, U401.1 ((PWM5/AD1.6/CAP1.3)P0.21)
RESET: R401.2 (1), S457.P$1 (1), U401.57 (RESET)
RTXC1: C403.4 (2), U401.3 (RTXC1), Y402.2
RTXC2: C403.2 (1), U401.5 (RTXC2), Y402.1
RX0: JP6.P$3 (RXI), U401.21 ((RXD0/PWM3/EINT0)P0.1)
RX_GPS: U401.33 ((TXD1/PWM4/A1.1)P0.8), U502.9 (IO_HI)
RX_I: J501.RX, U502.3 (IO_LO)
SCK0: J701.5 (SCK), U401.27 ((SCK0/CAP0.1/AD0.6)P0.4)
SCL0: R401.3 (1), U101.4 (SCK/SCL), U401.22 ((SCL0/CAP0.0)P0.2), U601.23 (SCL/SCLK), U901.14 (SCL/SCK)
SDA0: R401.4 (1), U101.3 (SDI/SDA), U401.26 ((SDA0/MAT0.0/EINT1)P0.3), U601.24 (SDA/SDI), U901.13 (SDA/SDI/SDIO)
TX0: JP6.P$2 (TXO), U401.19 ((TXD0/PWM1)P0.0)
TX_GPS: U401.34 ((RXD1/PWM6/EINT3)P0.9), U502.10 (IO_HI)
TX_O: J501.TX, U502.2 (IO_LO)
VBUS: C302.1, D302.1 (A1), JP6.P$4 (VCC), U301.4 (VIN)
VCC: C106.1, C106.3 (2), C201.1, C423.1, C443.1, C449.3 (2), C463.1, C608.1, C613.1, C901.1, C906.1, J701.4 (VCC), R401.5 (2), R401.6 (2), R401.7 (2), R401.8 (2), U101.2 (CSB), U101.6 (VDDIO), U101.8 (VDD), U201.1 (VO2), U401.7 (VDDA3), U401.23 (VDD3-1), U401.43 (VDD3-2), U401.51 (VDD3-3), U401.63 (VREF), U502.11 (VCC_HI), U601.1 (VDDIO), U601.8 (VDDIO), U601.13 (VDD), U601.22 (#CS), U901.1 (VDDIO), U901.6 (VS), U901.7 (CS)
VIN: C205.1, D302.3 (K), U201.3 (EN2), U201.4 (EN1), U201.5 (VIN)
VLIPO: C301.1, C449.4 (2), D302.2 (A2), J301.2, U301.3 (VBAT), U401.49 (VBAT)
XTAL1: C1.3 (2), U401.62 (XTAL1), Y401.3 (2)
XTAL2: C1.4 (2), U401.61 (XTAL2), Y401.1

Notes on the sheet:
Section 2 - Regulator
Section 4 - Controller
Section 7 - MicroSD
Section 1 - Baro/Temp sensor
Freq Cl Rs Cx1,Cx2
10MHz-15MHz 10pF <300 18pF
10MHz-15MHz 20pF <220 38pF
10MHz-15MHz 30pF <140 58pF
TXC inc 8Z 12MHz - 18pf Cl <100 Rs 30ppm/30ppm
at 18pF, exact Cx1 is 34pF, 33pF is closest E12
32kiHz 11pF <100k 18pF
32kiHz 13pF <100k 22pF
32kiHz 15pF <100k 27pF
Abracon ABS06 32kiHz - 12.5pf Cl <90k Rs 20ppm
at 12.5pF, exact Cx1 is 21pF, 22pF is closest E12
Section 3 - Charging circuit
Max charge current Ireg=1000V/R301
For R301=10k, Ireg=1000V/10000Ohm=0.1A
BSS138
Section 5 - GPS

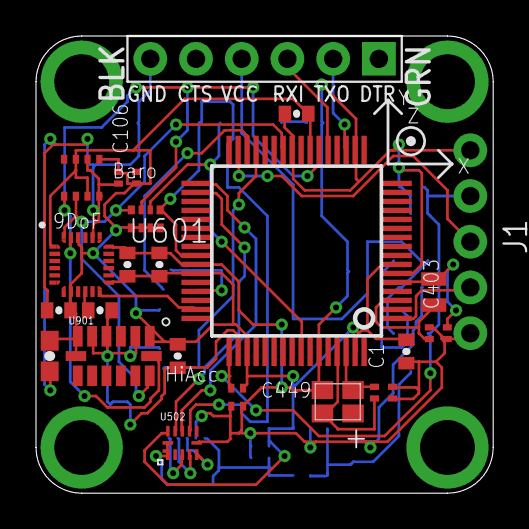
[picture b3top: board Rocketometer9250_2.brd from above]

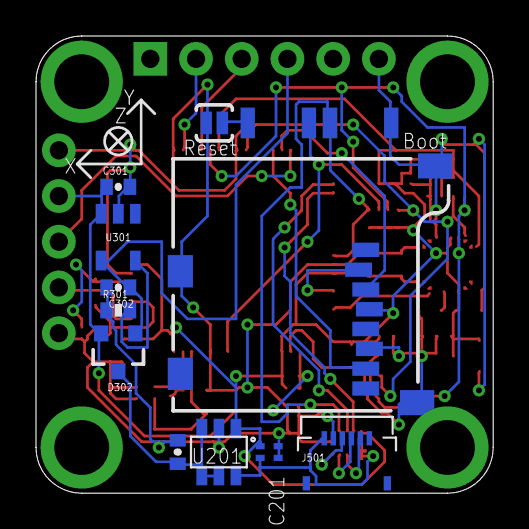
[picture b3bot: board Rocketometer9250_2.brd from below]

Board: 2 copper layers, 25.4 x 25.4 mm, 41 parts (14 on the bottom side), 33 nets.

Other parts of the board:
U$4: AXES

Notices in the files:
parts and their libraries:
SparkFun-Connectors: Licensing: CC v3.0 Share-Alike You are welcome to use this library for commercial purposes.
